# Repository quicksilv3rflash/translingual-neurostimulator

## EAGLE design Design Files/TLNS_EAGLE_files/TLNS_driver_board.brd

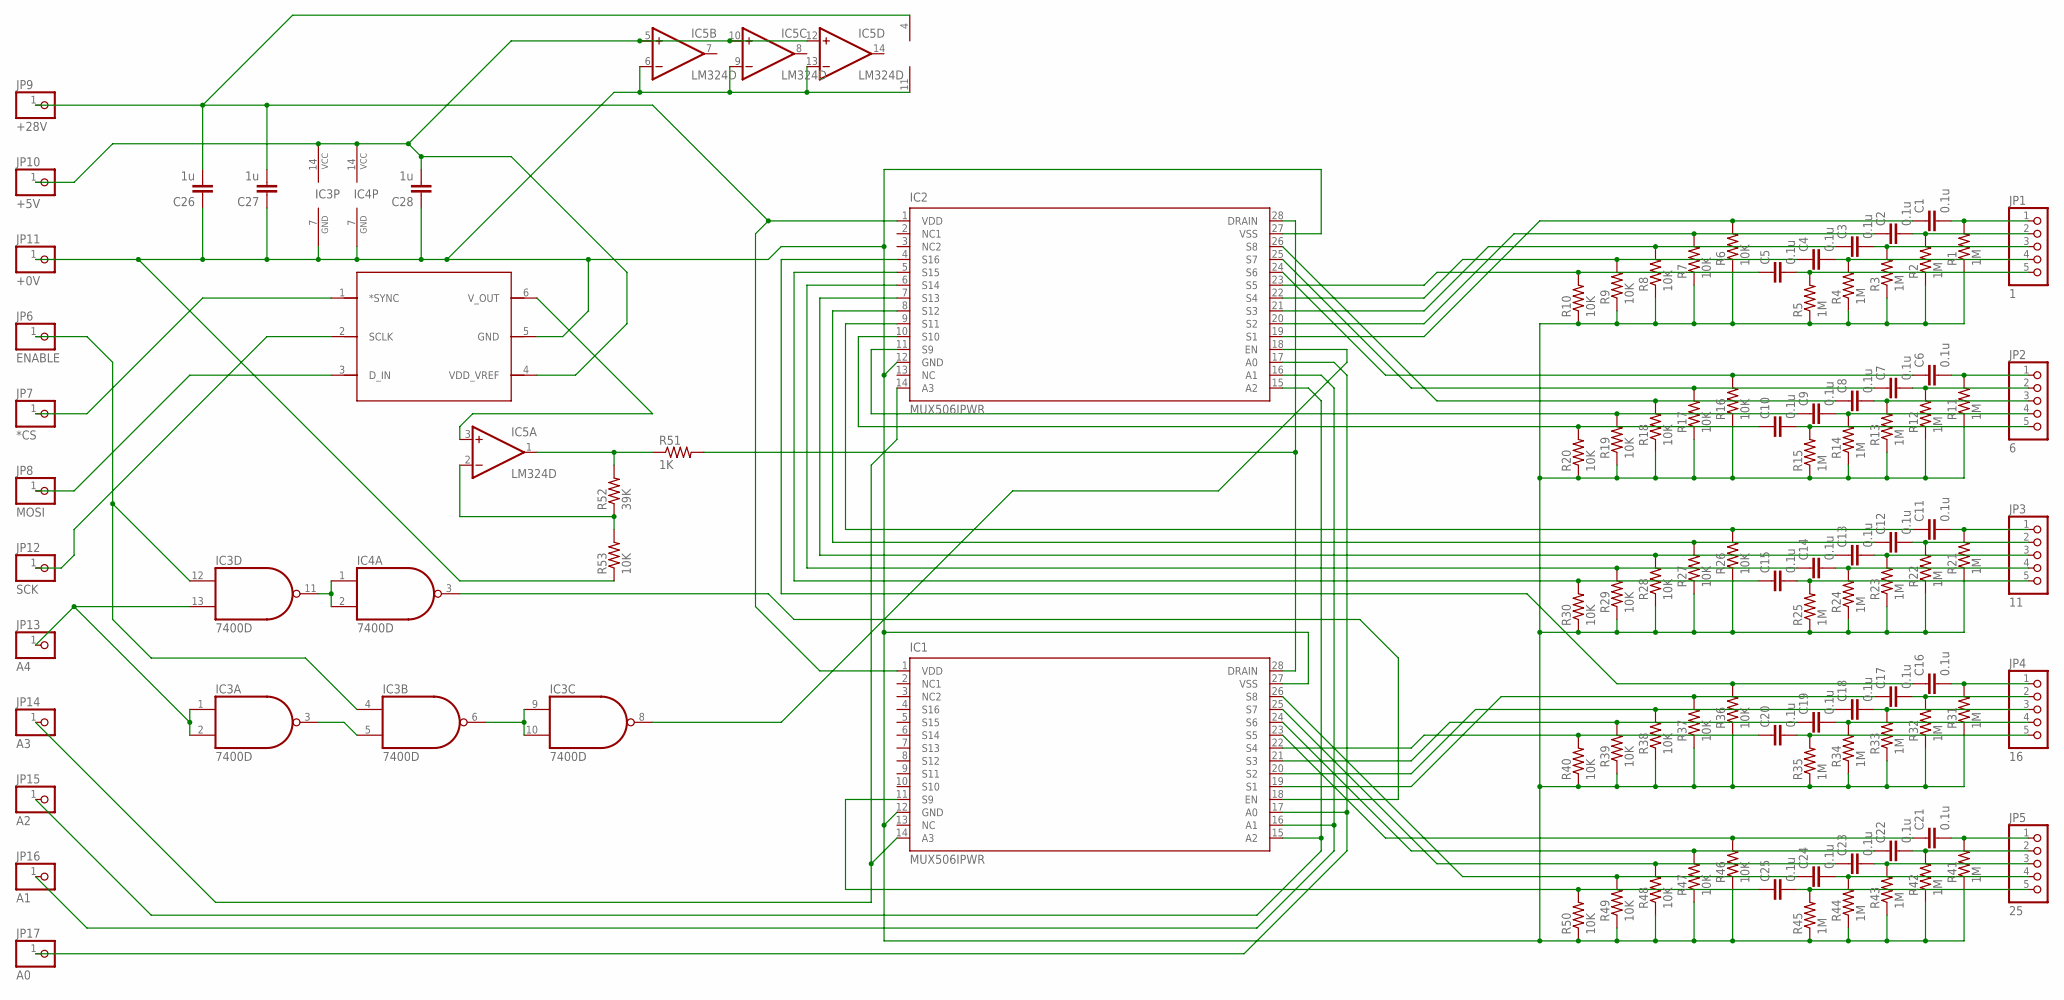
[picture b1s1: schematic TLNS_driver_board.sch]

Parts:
C1, C2, C3, C4, C5, C6, C7, C8, C9, C10, C11, C12, C13, C14, C15, C16, C17, C18, C19, C20, C21, C22, C23, C24, C25: 0.1u; C0603K
C26, C27, C28: 1u; C0603K
IC1, IC2: MUX506IPWR; SO28W
IC3, IC4: 7400D; SO14
IC5: LM324D; SO14
JP1: 1; 1X05
JP2: 6; 1X05
JP3: 11; 1X05
JP4: 16; 1X05
JP5: 25; 1X05
JP6: ENABLE; 1X01
JP7: *CS; 1X01
JP8: MOSI; 1X01
JP9: +28V; 1X01
JP10: +5V; 1X01
JP11: +0V; 1X01
JP12: SCK; 1X01
JP13: A4; 1X01
JP14: A3; 1X01
JP15: A2; 1X01
JP16: A1; 1X01
JP17: A0; 1X01
R1, R2, R3, R4, R5, R11, R12, R13, R14, R15, R21, R22, R23, R24, R25, R31, R32, R33, R34, R35, R41, R42, R43, R44, R45: 1M; R0603
R6, R7, R8, R9, R10, R16, R17, R18, R19, R20, R26, R27, R28, R29, R30, R36, R37, R38, R39, R40, R46, R47, R48, R49, R50, R53: 10K; R0603
R51: 1K; R1206
R52: 39K; R0603
U$1: DAC7311; SC70-6

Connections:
unnamed: C1.2, JP1.1, R1.2
unnamed: C2.2, JP1.2, R2.2
unnamed: C3.2, JP1.3, R3.2
unnamed: C4.2, JP1.4, R4.2
unnamed: C5.2, JP1.5, R5.2
unnamed: C26.1, C27.1, C28.1, IC1.12 (GND), IC1.27 (VSS), IC2.12 (GND), IC2.27 (VSS), IC3.7 (GND), IC4.7 (GND), IC5.6 (-IN), IC5.9 (-IN), IC5.11 (V-), IC5.13 (-IN), JP11.1, R1.1, R2.1, R3.1, R4.1, R5.1, R6.1, R7.1, R8.1, R9.1, R10.1, R11.1, R12.1, R13.1, R14.1, R15.1, R16.1, R17.1, R18.1, R19.1, R20.1, R21.1, R22.1, R23.1, R24.1, R25.1, R26.1, R27.1, R28.1, R29.1, R30.1, R31.1, R32.1, R33.1, R34.1, R35.1, R36.1, R37.1, R38.1, R39.1, R40.1, R41.1, R42.1, R43.1, R44.1, R45.1, R46.1, R47.1, R48.1, R49.1, R50.1, R53.1, U$1.5 (GND)
unnamed: C4.1, IC2.22 (S4), R9.2
unnamed: C3.1, IC2.21 (S3), R8.2
unnamed: C2.1, IC2.20 (S2), R7.2
unnamed: C1.1, IC2.19 (S1), R6.2
unnamed: C5.1, IC2.23 (S5), R10.2
unnamed: C6.2, JP2.1, R11.2
unnamed: C7.2, JP2.2, R12.2
unnamed: C8.2, JP2.3, R13.2
unnamed: C9.2, JP2.4, R14.2
unnamed: C10.2, JP2.5, R15.2
unnamed: C9.1, IC2.11 (S9), R19.2
unnamed: C8.1, IC2.26 (S8), R18.2
unnamed: C7.1, IC2.25 (S7), R17.2
unnamed: C6.1, IC2.24 (S6), R16.2
unnamed: IC1.28 (DRAIN), IC2.28 (DRAIN), R51.2
unnamed: C10.1, IC2.10 (S10), R20.2
unnamed: C11.2, JP3.1, R21.2
unnamed: C12.2, JP3.2, R22.2
unnamed: C13.2, JP3.3, R23.2
unnamed: C14.2, JP3.4, R24.2
unnamed: C15.2, JP3.5, R25.2
unnamed: C14.1, IC2.6 (S14), R29.2
unnamed: C13.1, IC2.7 (S13), R28.2
unnamed: C12.1, IC2.8 (S12), R27.2
unnamed: C11.1, IC2.9 (S11), R26.2
unnamed: IC3.11 (O), IC4.1 (I0), IC4.2 (I1)
unnamed: C15.1, IC2.5 (S15), R30.2
unnamed: C16.2, JP4.1, R31.2
unnamed: C17.2, JP4.2, R32.2
unnamed: C18.2, JP4.3, R33.2
unnamed: C19.2, JP4.4, R34.2
unnamed: C20.2, JP4.5, R35.2
unnamed: C19.1, IC1.21 (S3), R39.2
unnamed: C18.1, IC1.20 (S2), R38.2
unnamed: C17.1, IC1.19 (S1), R37.2
unnamed: C16.1, IC2.4 (S16), R36.2
unnamed: IC1.18 (EN), IC4.3 (O)
unnamed: C20.1, IC1.22 (S4), R40.2
unnamed: C21.2, JP5.1, R41.2
unnamed: C22.2, JP5.2, R42.2
unnamed: C23.2, JP5.3, R43.2
unnamed: C24.2, JP5.4, R44.2
unnamed: C25.2, JP5.5, R45.2
unnamed: C24.1, IC1.26 (S8), R49.2
unnamed: C23.1, IC1.25 (S7), R48.2
unnamed: C22.1, IC1.24 (S6), R47.2
unnamed: C21.1, IC1.23 (S5), R46.2
unnamed: C26.2, C27.2, IC1.1 (VDD), IC2.1 (VDD), IC5.4 (V+), JP9.1
unnamed: C25.1, IC1.11 (S9), R50.2
unnamed: IC1.17 (A0), IC2.17 (A0), JP17.1
unnamed: IC1.16 (A1), IC2.16 (A1), JP16.1
unnamed: IC1.15 (A2), IC2.15 (A2), JP15.1
unnamed: IC1.14 (A3), IC2.14 (A3), JP14.1
unnamed: IC3.1 (I0), IC3.2 (I1), IC3.13 (I1), JP13.1
unnamed: IC3.4 (I0), IC3.12 (I0), JP6.1
unnamed: C28.2, IC3.14 (VCC), IC4.14 (VCC), IC5.5 (+IN), IC5.10 (+IN), IC5.12 (+IN), JP10.1, U$1.4 (VDD_VREF)
unnamed: IC3.3 (O), IC3.5 (I1)
unnamed: IC3.6 (O), IC3.9 (I0), IC3.10 (I1)
unnamed: IC2.18 (EN), IC3.8 (O)
unnamed: IC5.1 (OUT), R51.1, R52.2
unnamed: IC5.2 (-IN), R52.1, R53.2
unnamed: JP8.1, U$1.3 (D_IN)
unnamed: JP12.1, U$1.2 (SCLK)
unnamed: JP7.1, U$1.1 (*SYNC)
unnamed: IC5.3 (+IN), U$1.6 (V_OUT)
S12: IC1.8 (S12)

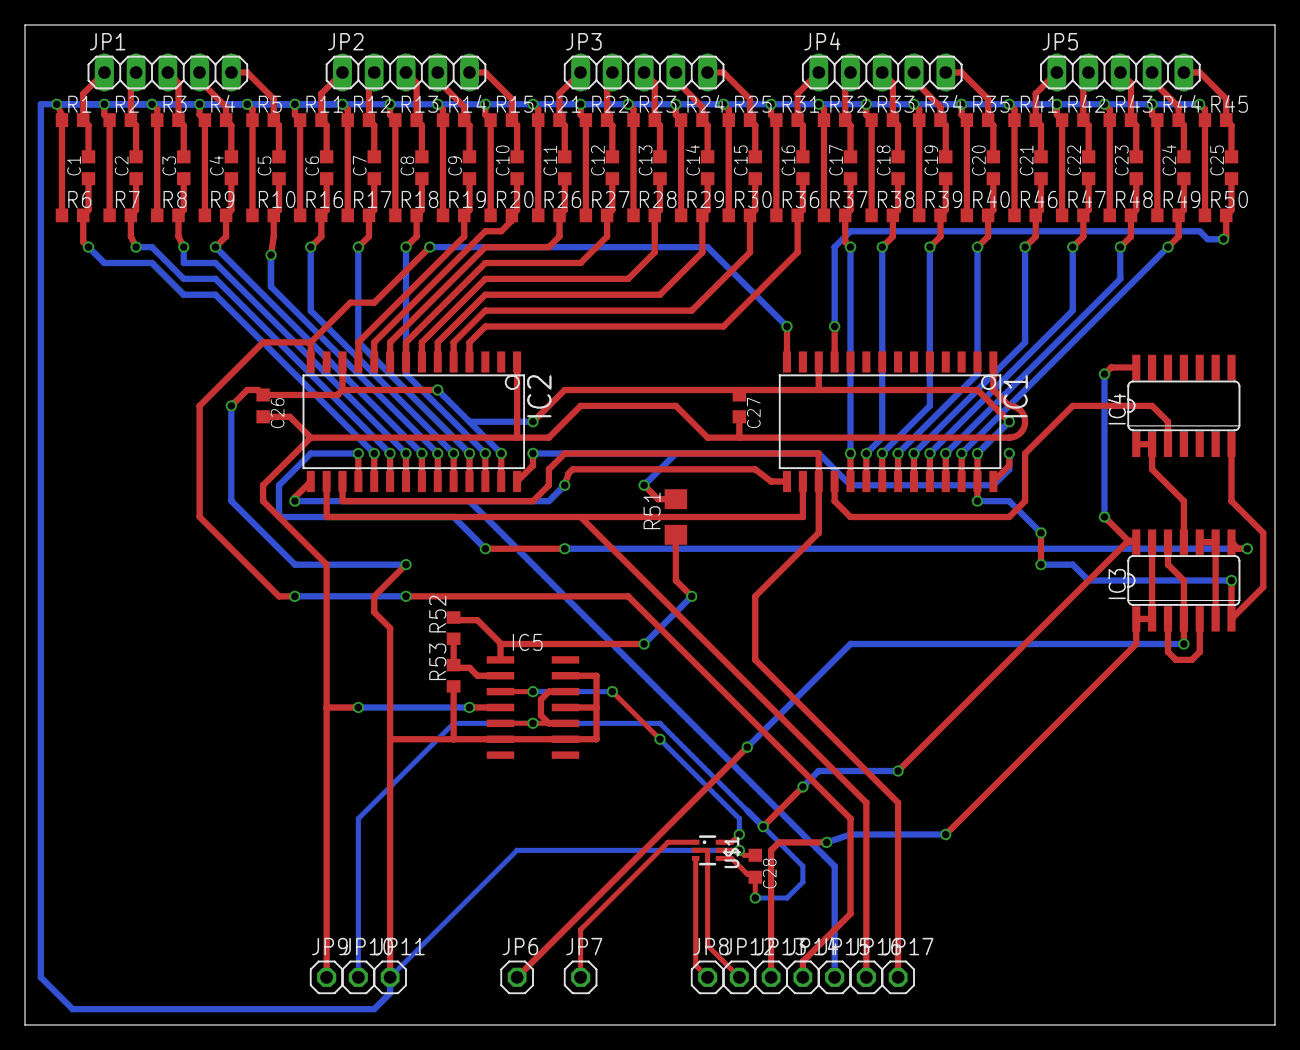
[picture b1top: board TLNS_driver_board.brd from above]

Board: 2 copper layers, 100.0 x 80.0 mm, 104 parts (0 on the bottom side), 71 nets.

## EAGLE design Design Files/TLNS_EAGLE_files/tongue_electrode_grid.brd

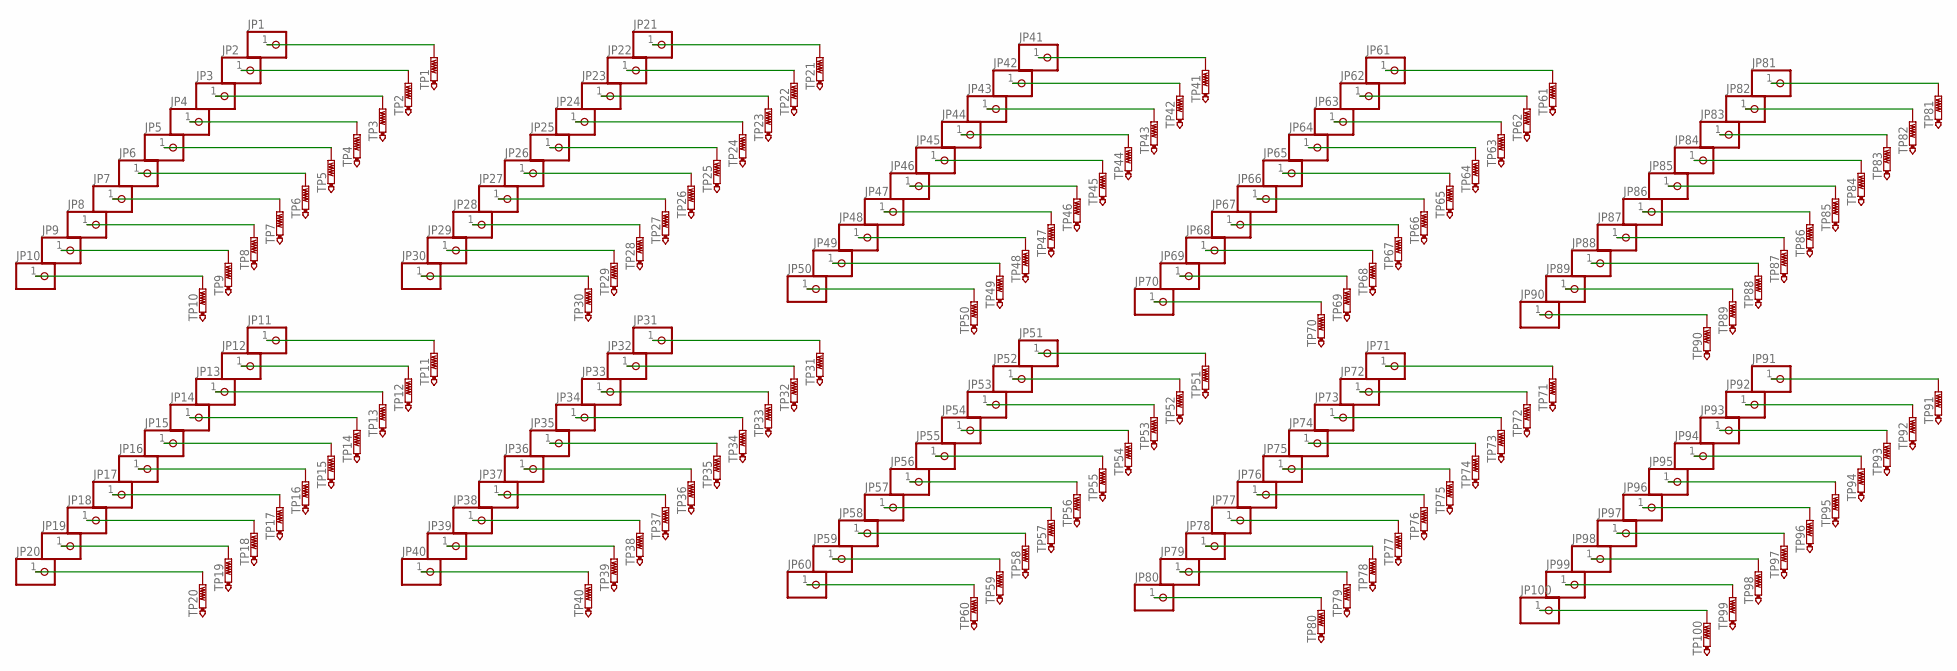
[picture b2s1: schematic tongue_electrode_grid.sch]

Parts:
JP1, JP2, JP3, JP4, JP5, JP6, JP7, JP8, JP9, JP10, JP11, JP12, JP13, JP14, JP15, JP16, JP17, JP18, JP19, JP20, JP21, JP22, JP23, JP24, JP25, JP26, JP27, JP28, JP29, JP30, JP31, JP32, JP33, JP34, JP35, JP36, JP37, JP38, JP39, JP40, JP41, JP42, JP43, JP44, JP45, JP46, JP47, JP48, JP49, JP50, JP51, JP52, JP53, JP54, JP55, JP56, JP57, JP58, JP59, JP60, JP61, JP62, JP63, JP64, JP65, JP66, JP67, JP68, JP69, JP70, JP71, JP72, JP73, JP74, JP75, JP76, JP77, JP78, JP79, JP80, JP81, JP82, JP83, JP84, JP85, JP86, JP87, JP88, JP89, JP90, JP91, JP92, JP93, JP94, JP95, JP96, JP97, JP98, JP99, JP100: PINHD-1X1; 1X01
TP1, TP2, TP3, TP4, TP5, TP6, TP7, TP8, TP9, TP10, TP11, TP12, TP13, TP14, TP15, TP16, TP17, TP18, TP19, TP20, TP21, TP22, TP23, TP24, TP25, TP26, TP27, TP28, TP29, TP30, TP31, TP32, TP33, TP34, TP35, TP36, TP37, TP38, TP39, TP40, TP41, TP42, TP43, TP44, TP45, TP46, TP47, TP48, TP49, TP50, TP51, TP52, TP53, TP54, TP55, TP56, TP57, TP58, TP59, TP60, TP61, TP62, TP63, TP64, TP65, TP66, TP67, TP68, TP69, TP70, TP71, TP72, TP73, TP74, TP75, TP76, TP77, TP78, TP79, TP80, TP81, TP82, TP83, TP84, TP85, TP86, TP87, TP88, TP89, TP90, TP91, TP92, TP93, TP94, TP95, TP96, TP97, TP98, TP99, TP100: PTR1TP11R; TP11R

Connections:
unnamed: JP1.1, TP1.TP
unnamed: JP2.1, TP2.TP
unnamed: JP3.1, TP3.TP
unnamed: JP4.1, TP4.TP
unnamed: JP5.1, TP5.TP
unnamed: JP6.1, TP6.TP
unnamed: JP7.1, TP7.TP
unnamed: JP8.1, TP8.TP
unnamed: JP9.1, TP9.TP
unnamed: JP10.1, TP10.TP
unnamed: JP11.1, TP11.TP
unnamed: JP12.1, TP12.TP
unnamed: JP13.1, TP13.TP
unnamed: JP14.1, TP14.TP
unnamed: JP15.1, TP15.TP
unnamed: JP16.1, TP16.TP
unnamed: JP17.1, TP17.TP
unnamed: JP18.1, TP18.TP
unnamed: JP19.1, TP19.TP
unnamed: JP20.1, TP20.TP
unnamed: JP21.1, TP21.TP
unnamed: JP22.1, TP22.TP
unnamed: JP23.1, TP23.TP
unnamed: JP24.1, TP24.TP
unnamed: JP25.1, TP25.TP
unnamed: JP26.1, TP26.TP
unnamed: JP27.1, TP27.TP
unnamed: JP28.1, TP28.TP
unnamed: JP29.1, TP29.TP
unnamed: JP30.1, TP30.TP
unnamed: JP31.1, TP31.TP
unnamed: JP32.1, TP32.TP
unnamed: JP33.1, TP33.TP
unnamed: JP34.1, TP34.TP
unnamed: JP35.1, TP35.TP
unnamed: JP36.1, TP36.TP
unnamed: JP37.1, TP37.TP
unnamed: JP38.1, TP38.TP
unnamed: JP39.1, TP39.TP
unnamed: JP40.1, TP40.TP
unnamed: JP41.1, TP41.TP
unnamed: JP42.1, TP42.TP
unnamed: JP43.1, TP43.TP
unnamed: JP44.1, TP44.TP
unnamed: JP45.1, TP45.TP
unnamed: JP46.1, TP46.TP
unnamed: JP47.1, TP47.TP
unnamed: JP48.1, TP48.TP
unnamed: JP49.1, TP49.TP
unnamed: JP50.1, TP50.TP
unnamed: JP51.1, TP51.TP
unnamed: JP52.1, TP52.TP
unnamed: JP53.1, TP53.TP
unnamed: JP54.1, TP54.TP
unnamed: JP55.1, TP55.TP
unnamed: JP56.1, TP56.TP
unnamed: JP57.1, TP57.TP
unnamed: JP58.1, TP58.TP
unnamed: JP59.1, TP59.TP
unnamed: JP60.1, TP60.TP
unnamed: JP61.1, TP61.TP
unnamed: JP62.1, TP62.TP
unnamed: JP63.1, TP63.TP
unnamed: JP64.1, TP64.TP
unnamed: JP65.1, TP65.TP
unnamed: JP66.1, TP66.TP
unnamed: JP67.1, TP67.TP
unnamed: JP68.1, TP68.TP
unnamed: JP69.1, TP69.TP
unnamed: JP70.1, TP70.TP
unnamed: JP71.1, TP71.TP
unnamed: JP72.1, TP72.TP
unnamed: JP73.1, TP73.TP
unnamed: JP74.1, TP74.TP
unnamed: JP75.1, TP75.TP
unnamed: JP76.1, TP76.TP
unnamed: JP77.1, TP77.TP
unnamed: JP78.1, TP78.TP
unnamed: JP79.1, TP79.TP
unnamed: JP80.1, TP80.TP
unnamed: JP81.1, TP81.TP
unnamed: JP82.1, TP82.TP
unnamed: JP83.1, TP83.TP
unnamed: JP84.1, TP84.TP
unnamed: JP85.1, TP85.TP
unnamed: JP86.1, TP86.TP
unnamed: JP87.1, TP87.TP
unnamed: JP88.1, TP88.TP
unnamed: JP89.1, TP89.TP
unnamed: JP90.1, TP90.TP
unnamed: JP91.1, TP91.TP
unnamed: JP92.1, TP92.TP
unnamed: JP93.1, TP93.TP
unnamed: JP94.1, TP94.TP
unnamed: JP95.1, TP95.TP
unnamed: JP96.1, TP96.TP
unnamed: JP97.1, TP97.TP
unnamed: JP98.1, TP98.TP
unnamed: JP99.1, TP99.TP
unnamed: JP100.1, TP100.TP

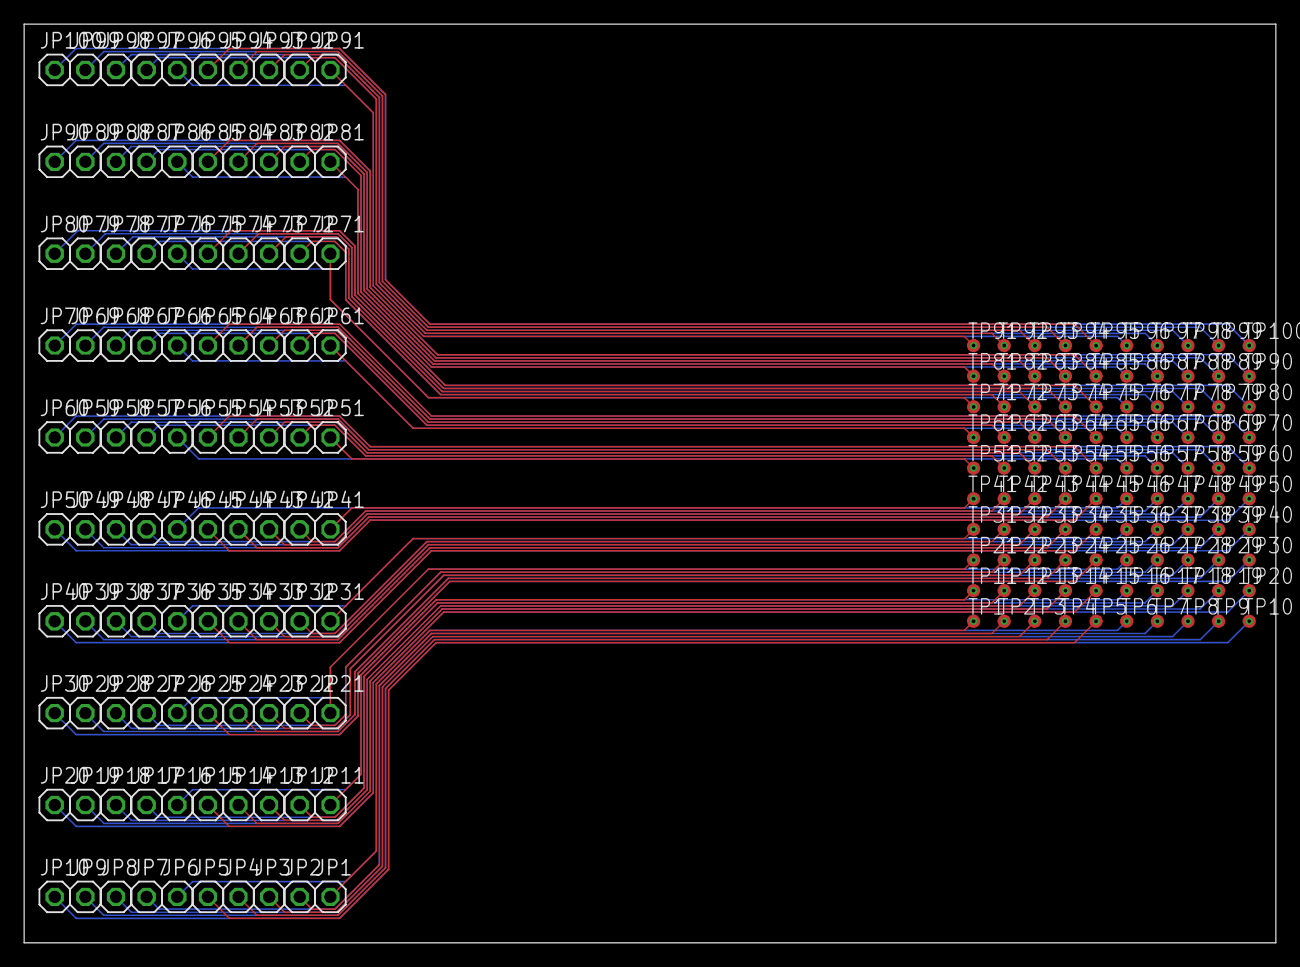
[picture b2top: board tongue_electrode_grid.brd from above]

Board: 2 copper layers, 103.8 x 76.2 mm, 200 parts (0 on the bottom side), 100 nets.

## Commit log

2018-09-02 Awaiting shipment of driver boards
2018-09-02 Awaiting shipment of driver boards. No firmware yet written.
